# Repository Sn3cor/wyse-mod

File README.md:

# wyse-mod
This project makes converting Wyse keyboards (with 4P4C connector) easier to test, with the end goal of functioning as a standalone converter box. It is designed to work with [Soarer's Wyse conversion software](https://geekhack.org/index.php?topic=52597.0). I'll be trying to create something similar soon (to be at least compatible with Wyse PCE Keyboard).

Huge thanks to [ErkHal](https://github.com/ErkHal) and their [Pohola Work's project](https://github.com/pohjolaworks/wyse-converter) for sparking the idea for this project.

# Overview
The PCB features dedicated pads to solder wires straight from the keyboards connector pins for easy testing.

A Pro Micro microcontroller is mounted on the bottom of the board, with components facing the PCB. Also using a socket for an MCU is highly recommended. After veryfing that your Wyse keyboard works with the firmware, simply solder a 4P4C connector and plug in an old RJ9/RJ10/RJ22 (afaik they are all the same) roll-over (crossed) cable.

## Frontside

## Backside

# Parts List
- the PCB
- Pro Micro like board (with ATmega32U4) 
- Hotswap sockets for the Pro Micro
- 4P4C connector
- RJ9/RJ10/RJ22 cable
- 6x6 button (optional, but makes flashing software easier)
- 4xM3 screws (TODO after designing a case)

# TODO
- [x] Design a PCB [Rev 1.0 is being tested]
- [ ] Design a case
- [ ] Try to write own conversion software

# Sources and helpful links
- [Soarer's geekhack thread](https://geekhack.org/index.php?topic=51079.msg1127174#msg1127174)(some of the images aren't rendering so [here is an archived version](https://web.archive.org/web/20230822022830/https://geekhack.org/index.php?topic=51079.0))
- [Soarer's deskthority thread](https://deskthority.net/viewtopic.php?t=7424)
- [A guide for Pro Micro conversion with Soarer's](https://jorts.tech/projects/promicro-soarers-guide)(contains a thorough guide for the Soarer's mod and mentions other useful sources)

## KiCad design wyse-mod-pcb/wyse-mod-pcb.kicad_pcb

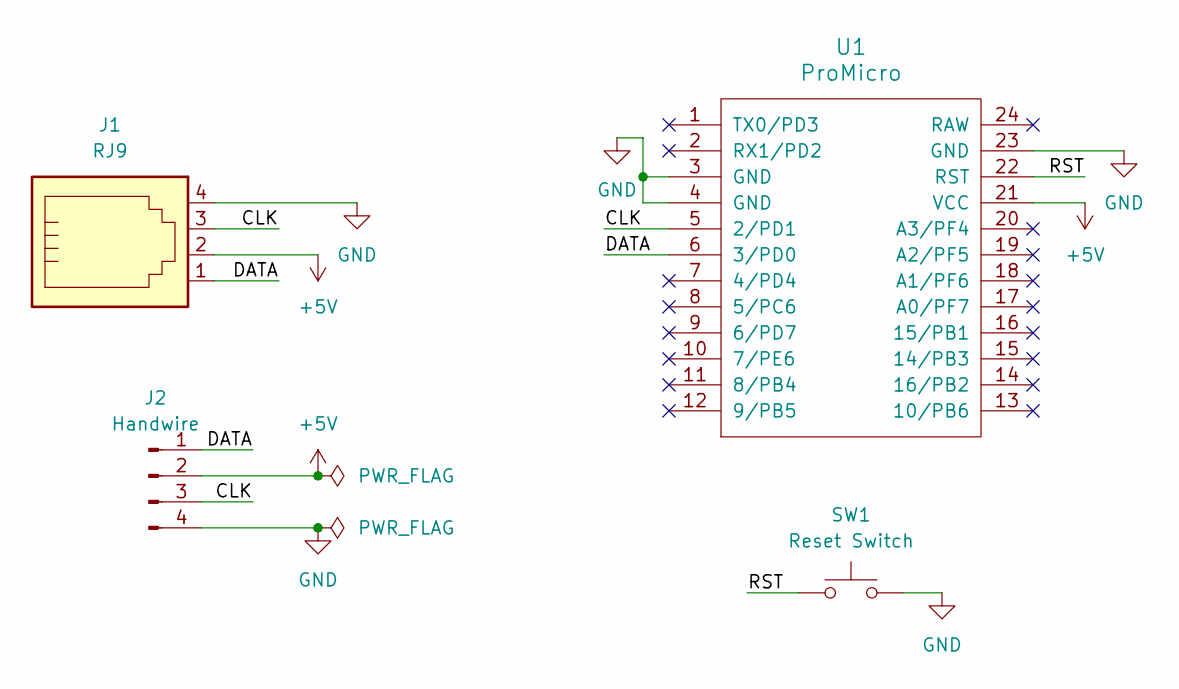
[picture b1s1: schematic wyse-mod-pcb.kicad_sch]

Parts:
J1: RJ9; RJ9_Evercom_5301-440xxx_Horizontal
J2: Handwire; PinSocket_1x04_P2.54mm_Vertical
SW1: Reset Switch; SW_PUSH_6mm
U1: ProMicro; ArduinoProMicro

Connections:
+5V: J1.2, J2.2, U1.21 (VCC)
/CLK: J1.3, J2.3, U1.5 (2/PD1)
/DATA: J1.1, J2.1, U1.6 (3/PD0)
/RST: SW1.1, U1.22 (RST)
GND: J1.4, J2.4, SW1.2, U1.3 (GND), U1.4 (GND), U1.23 (GND)

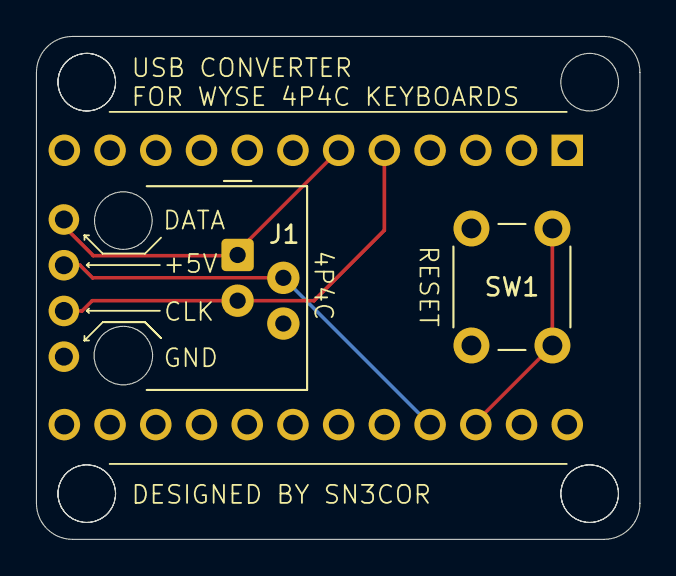
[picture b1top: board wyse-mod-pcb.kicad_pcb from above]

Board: 2 copper layers, 33.5 x 27.9 mm, 4 parts (0 on the bottom side), 5 nets.
